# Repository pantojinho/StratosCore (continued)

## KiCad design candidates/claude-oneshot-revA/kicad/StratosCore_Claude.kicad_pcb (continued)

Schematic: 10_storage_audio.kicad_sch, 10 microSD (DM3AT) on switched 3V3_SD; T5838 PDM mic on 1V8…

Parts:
C120, C123: 100pF; C_0402_1005Metric
C121: 10uF; C_0603_1608Metric
C122, C125, C126: 100nF; C_0402_1005Metric
C124: 1uF; C_0402_1005Metric
C127: 100nF X7R; C_0402_1005Metric
J8: DM3AT-SF-PEJM5; Hirose_DM3AT-SF-PEJM5_microSD_HC; MPN DM3AT-SF-PEJM5
MK1: MMICT5838-00-012; TDK_T5838_LGA-7_3.5x2.65mm_BottomPort; MPN MMICT5838-00-012
R100, R104, R105, R106: 100k; R_0402_1005Metric
R101, R102, R103: 10k; R_0402_1005Metric
R107, R108: 47k; R_0402_1005Metric
TP27, TP28: TP; TestPoint_Pad_D1.0mm
U10, U12: TPS22918DBVR; TI_DBV0006A_SOT-23-6_TPS22918; MPN TPS22918DBVR
U23: TPD4E05U06DQAR; USON-10_2.5x1.0mm_P0.5mm; MPN TPD4E05U06DQARG4
U24: TXU0202DCUR; TI_DCU0008A_VSSOP-8_2.3x2mm_P0.5mm_TXU0202; MPN TXU0202DCUR

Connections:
1V8_AUDIO_SW: C124.1, C126.1, C127.1, MK1.7 (VDD), R106.2, U12.5 (QOD), U12.6 (VOUT), U24.7 (VCCB)
1V8_LOGIC: U12.1 (VIN); also elsewhere on the board
3V3_MAIN: C125.1, R104.2, U10.1 (VIN), U24.3 (VCCA); also elsewhere on the board
3V3_SD: C121.1, C122.1, J8.4 (VDD), R101.2, R102.2, R103.2, R107.2, R108.2, TP27.1, U10.5 (QOD), U10.6 (VOUT)
AUD_CT: C123.1, U12.4 (CT)
AUD_SW_EN: R105.1, U12.3 (ON); also elsewhere on the board
GND: C120.2, C121.2, C122.2, C123.2, C124.2, C125.2, C126.2, C127.2, J8.6 (VSS), J8.10 (DET_A), J8.SH (SHIELD), MK1.2 (SELECT), MK1.3 (GND), MK1.5 (THSEL), R100.2, R105.2, U10.2 (GND), U12.2 (GND), U23.3 (GND), U23.8 (GND), U24.2 (GND); also elsewhere on the board
PDM_CLK: U24.5 (A1); also elsewhere on the board
PDM_CLK_1V8: MK1.6 (CLK), U24.8 (B1Y)
PDM_DATA: U24.4 (A2Y); also elsewhere on the board
PDM_DATA_1V8: MK1.1 (DATA), U24.1 (B2)
PDM_OE: R106.1, U24.6 (OE)
SD_CD: J8.9 (DET_B), R104.1, TP28.1; also elsewhere on the board
SD_CS: J8.2 (DAT3/CD), R101.1, U23.1 (D1+), U23.10 (NC); also elsewhere on the board
SD_CT: C120.1, U10.4 (CT)
SD_DAT1: J8.8 (DAT1), R107.1
SD_DAT2: J8.1 (DAT2), R108.1
SD_SW_EN: R100.1, U10.3 (ON); also elsewhere on the board
SPI_MISO: J8.7 (DAT0), R103.1, U23.5 (D2-), U23.6 (NC); also elsewhere on the board
SPI_MOSI: J8.3 (CMD), R102.1, U23.2 (D1-), U23.9 (NC); also elsewhere on the board
SPI_SCLK: J8.5 (CLK), U23.4 (D2+), U23.7 (NC); also elsewhere on the board

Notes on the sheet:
10 microSD (DM3AT) on switched 3V3_SD; T5838 PDM mic on 1V8_AUDIO_SW
DIG-02: SPI mode (DAT3 = SD_CS), 10k pull-ups on CMD/DAT0/DAT3 to 3V3_SD (never 3V3_MAIN), no CLK pull-up, card detect 100k to 3V3_MAIN on TCA P00, TPD4E05U06 at the socket.
AUD-01/AUD-02: 1V8_AUDIO_SW = TPS22918 branch from 1V8_LOGIC (AUD_SW_EN, pull-down). TXU0202 A1->B1Y clock, B2->A2Y data, OE 100k to 1V8_AUDIO_SW.
T5838 SELECT=GND (DATA1/right), THSEL=GND and WAKE open (no AAD). 0.8 mm sound hole in the footprint, no paste on the port.

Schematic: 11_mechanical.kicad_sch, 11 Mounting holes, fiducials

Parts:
FID1, FID2, FID3: Fiducial; Fiducial_1mm_Mask2mm
H1, H2, H3: M2.5; MountingHole_2.7mm_M2.5

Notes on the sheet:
11 Mounting holes, fiducials
Three M2.5 mounting holes in the left strip (the 2S holder covers the back for x > 14.7 mm; holder is fixed to the rear shell); three fiducials.

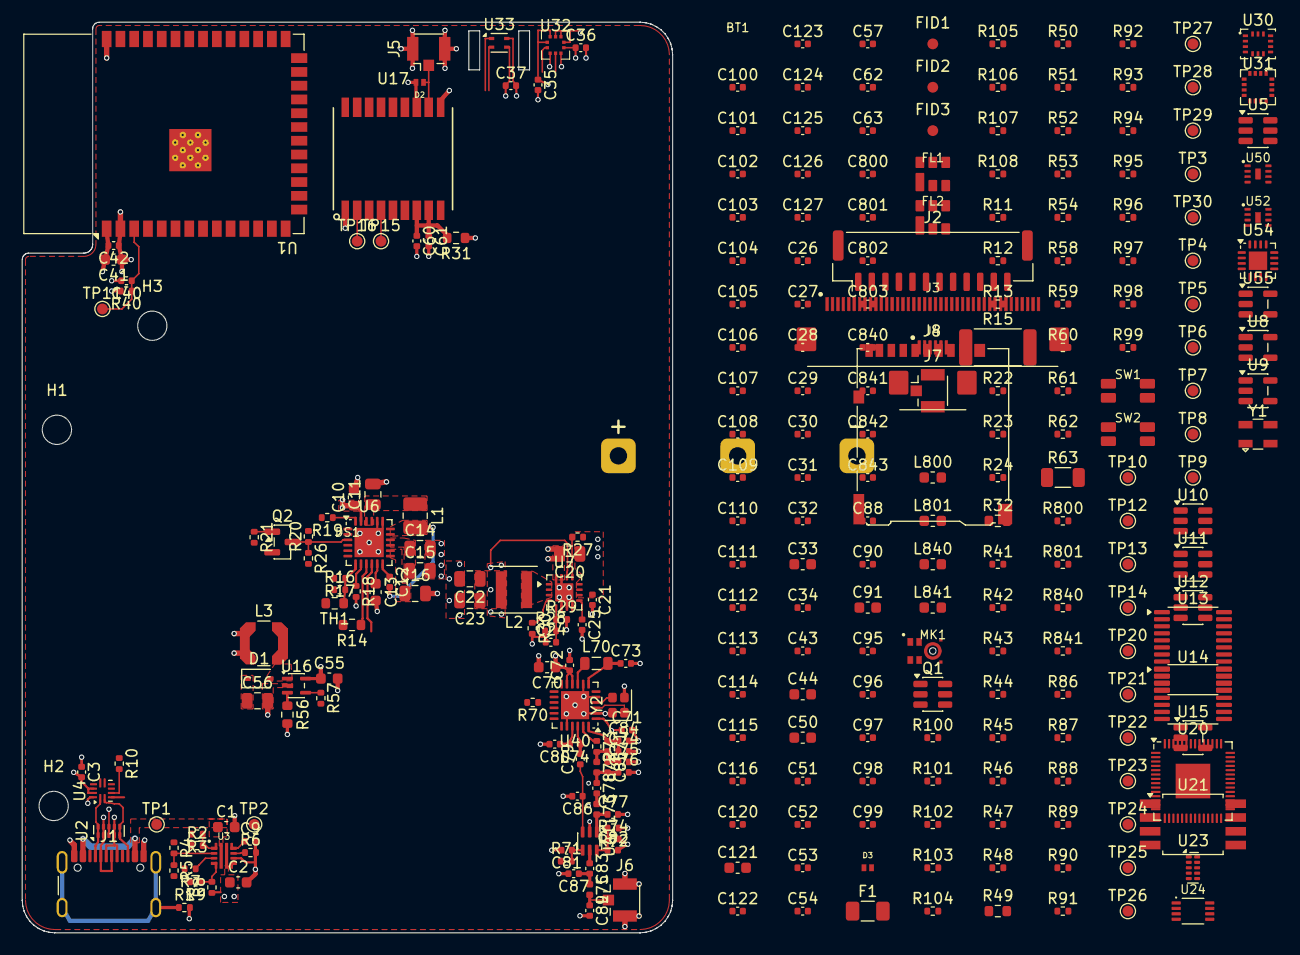
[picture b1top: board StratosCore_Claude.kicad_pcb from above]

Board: 4 copper layers, 60.0 x 84.0 mm, 293 parts (0 on the bottom side), 178 nets.

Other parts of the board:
DS1: display envelope; Display_Orient_AFY240320A1-2.8INTH-C1_Envelope

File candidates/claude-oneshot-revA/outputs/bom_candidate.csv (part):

"Refs","Value","Footprint","MPN","Status","Source","Qty","DNP"
"BT1","2S 21700 holder (MPN TBD)","SC:BatteryHolder_2S_21700_TBD","TBD","OWNER DIRECTION - MPN/REVIEW TBD","","1",""
"C1,C2","1uF 25V X7R","Capacitor_SMD:C_0603_1608Metric","","","","2",""
"C3,C30,C35-C37,C42,C43,C51-C54,C57,C61-C63,C72,C97,C100-C107,C110-C113,C116,C122,C125,C126","100nF","Capacitor_SMD:C_0402_1005Metric","","ADC_AVDD,USB_VDD","","33",""
"C9","TBD (O06)","Capacitor_SMD:C_0402_1005Metric","","ITIMER value TBD at O06","","1","DNP"
"C10","1uF 25V","Capacitor_SMD:C_0603_1608Metric","","","","1",""
"C11","10uF 25V","Capacitor_SMD:C_0805_2012Metric","","","","1",""
"C12,C95,C96","47nF","Capacitor_SMD:C_0402_1005Metric","","","","3",""
"C13,C55","4.7uF 10V","Capacitor_SMD:C_0603_1608Metric","","","","2",""
"C14,C15","22uF 16V","Capacitor_SMD:C_0805_2012Metric","","","","2",""
"C16","10uF 16V","Capacitor_SMD:C_0805_2012Metric","","","","1",""
"C20","10uF 25V X7R","Capacitor_SMD:C_0805_2012Metric","","","","1",""
"C21","100nF 25V","Capacitor_SMD:C_0402_1005Metric","","","","1",""
"C22,C23","22uF 6.3V X7R","Capacitor_SMD:C_0805_2012Metric","","second output cap; DC-bias review","","2",""
"C24,C25","3.3nF","Capacitor_SMD:C_0402_1005Metric","","feed-forward per repo text; review","","2",""
"C26-C29,C34,C40,C108,C109,C124","1uF","Capacitor_SMD:C_0402_1005Metric","","VREG_VIN,VREG_VOUT","","9",""
"C31","2.2uF","Capacitor_SMD:C_0402_1005Metric","","","","1",""
"C32","10nF","Capacitor_SMD:C_0402_1005Metric","","VDDIO decoupling (DS)","","1",""
"C33,C41,C44,C50,C70,C91,C121","10uF","Capacitor_SMD:C_0603_1608Metric","","SET/RESET capacitor per DS","","7",""
"C56","1uF 50V X7R","Capacitor_SMD:C_0805_2012Metric","","","","1",""
"C60","1uF X7R","Capacitor_SMD:C_0402_1005Metric","","","","1",""
"C71,C73","470nF","Capacitor_SMD:C_0402_1005Metric","","VREG decoupling; value per E449 BOM TBD","","2",""
"C74-C80,C83","TBD (E449)","Capacitor_SMD:C_0402_1005Metric","","DC block to PE4259 RF1; value TBD,RX balun series C; value TBD,RX balun shunt; value TBD,TX match shunt; value TBD,VR_PA decoupling; value TBD,antenna DC block; value TBD,pi-filter shunt; value TBD","","8",""
"C81,C82","1nF","Capacitor_SMD:C_0402_1005Metric","","AN1200.40 C14,AN1200.40 C15","","2",""
"C88","100nF","Capacitor_SMD:C_0402_1005Metric","","","","1","DNP"
"C90,C98,C120,C123,C800,C802,C840,C842","100pF","Capacitor_SMD:C_0402_1005Metric","","BLB01 EVB C1,BLB01 EVB C4","","8",""
"C99","1nF","Capacitor_SMD:C_0402_1005Metric","","basic value 1nF slows pulses; DNP pending bench","","1","DNP"
"C114,C115","15pF C0G","Capacitor_SMD:C_0402_1005Metric","","","","2",""
"C127","100nF X7R","Capacitor_SMD:C_0402_1005Metric","","DS: 0.1uF at pin 7","","1",""
"C801,C803,C841,C843","12pF","Capacitor_SMD:C_0402_1005Metric","","BLB01 EVB C2 (RF out),BLB01 EVB C3","","4",""
"D1","60V Schottky TBD","Diode_SMD:D_SOD-123F","","exact 60 V-class part TBD (open)","","1",""
"D2","TPD1E0B04DPYR","SC:TI_TPD1E0B04DPYR_X1SON-2_DPY0002A","TPD1E0B04DPYR","","","1",""
"D3","TPD1E0B04DPYR (option)","SC:TI_TPD1E0B04DPYR_X1SON-2_DPY0002A","","ESD option at ADS-B input - DNP until RF review","","1","DNP"
"F1","TBD (O05)","Fuse:Fuse_1206_3216Metric","","Rating/type TBD by qualified review (O05)","","1",""
"FL1,FL2","TA2003A 1090MHz SAW","SC:TAI-SAW_TA2003A_SMD-6_3.0x3.0mm","TA2003A","","","2",""
"J1","USB4105-GF-A","Connector_USB:USB_C_Receptacle_GCT_USB4105-xx-A_16P_TopMnt_Horizontal","USB4105-GF-A","PREFERRED CANDIDATE - drawing B4 second pass open","https://gct.co/files/drawings/usb4105.pdf","1",""
"J2","BM12B-GHS-TBT (expansion)","Connector_JST:JST_GH_BM12B-GHS-TBT_1x12-1MP_P1.25mm_Vertical","BM12B-GHS-TBT","pinout = CONNECTOR_ARCHITECTURE.md; ESD/hot-plug TBD","","1",""
"J3","XF3M-4015-1B (TFT 40p FPC)","SC:Omron_XF3M-4015-1B_1x40-1MP_P0.5mm_Horizontal","XF3M-4015-1B","SAMPLE/CONTROLLED-DRAWING HOLD (O01); footprint from Omron G146-E1 lands","","1",""
"J4","XF3M-0615-1B (CTP 6p FPC)","SC:Omron_XF3M-0615-1B_1x06-1MP_P0.5mm_Horizontal","XF3M-0615-1B","SAMPLE HOLD; ST1633I address 0x70 convention open","","1",""
"J5","U.FL-R-SMT-1(60) GNSS","SC:Hirose_U.FL-R-SMT-1_60_Vertical","U.FL-R-SMT-1(60)","","","1",""
"J6","U.FL-R-SMT-1(60) LoRa","SC:Hirose_U.FL-R-SMT-1_60_Vertical","U.FL-R-SMT-1(60)","","","1",""
"J7","U.FL-R-SMT-1(60) ADS-B","SC:Hirose_U.FL-R-SMT-1_60_Vertical","U.FL-R-SMT-1(60)","","","1",""
"J8","DM3AT-SF-PEJM5","SC:Hirose_DM3AT-SF-PEJM5_microSD_HC","DM3AT-SF-PEJM5","","Hirose drawing 0000947170 Rev 4","1",""
"L1","1uH (DFE252012F-1R0 class)","Inductor_SMD:L_1008_2520Metric","","TI Fig.69 value; saturation/DCR review","","1",""
"L2","2.2uH XFL4020-222MEB","SC:L_Coilcraft_XxL4020","XFL4020-222MEB","","","1",""
"L3","10uH LPS4018-103MRC","SC:L_Coilcraft_LPS4018","LPS4018-103MRC","","","1",""
"L70","15uH (DC-DC)","Inductor_SMD:L_0805_2012Metric","","AN1200.40 L7 15uH; exact part/ISAT TBD","","1",""
"L71-L74","TBD (E449)","Inductor_SMD:L_0402_1005Metric","","PA supply choke VR_PA->RFO; value TBD,RX balun series L; value TBD,TX match/notch series; value TBD,pi-filter series; value TBD","","4",""
"L800,L840","27nH","Inductor_SMD:L_0603_1608Metric","","BLB01 EVB L1","","2",""
"L801,L841","82nH","Inductor_SMD:L_0603_1608Metric","","BLB01 EVB L2","","2",""
"MK1","MMICT5838-00-012","SC:TDK_T5838_LGA-7_3.5x2.65mm_BottomPort","MMICT5838-00-012","PREFERRED CANDIDATE - acoustic/footprint review","","1",""
"Q1","Dual N-MOSFET TBD (O05)","Package_TO_SOT_SMD:SOT-23-6","","PLACEHOLDER - FET selection/SOA/package TBD (O05)","","1",""
"Q2","2N7002","Package_TO_SOT_SMD:SOT-23","","","","1",""
"R1,R53-R55,R96,R801,R841","0R","Resistor_SMD:R_0402_1005Metric","","BLB01 EVB R2,GPIO8 host control of translator OE (optional),Shield/chassis treatment TBD,unused RD tie TBD,unused WR(D/CX) tie TBD","","7",""
"R2,R8","232k 1%","Resistor_SMD:R_0402_1005Metric","","one-shot candidate","","2",""
"R3,R5,R9,R29","100k 1%","Resistor_SMD:R_0402_1005Metric","","one-shot candidate","","4",""
"R4","442k 1%","Resistor_SMD:R_0402_1005Metric","","","","1",""
"R6","1.69k 1%","Resistor_SMD:R_0402_1005Metric","","","","1",""
"R7,R11-R13,R20,R21,R27,R30,R46-R48,R51,R57,R70,R90,R100,R104-R106","100k","Resistor_SMD:R_0402_1005Metric","","P10 default released,default OFF,default OFF (DIG-03),fail-safe: charge disabled","","19",""
"R10","900k 1%","Resistor_SMD:R_0402_1005Metric","","data-sheet 900k","","1",""
"R14","300R","Resistor_SMD:R_0603_1608Metric","","TI reverse-bottom-cell limiter","","1",""
"R15","TBD (RCBSET)","Resistor_SMD:R_2512_6332Metric","","balance current TBD; 40.8R/0.41W at 100 mA planning point","","1",""
"R16","5.23k 1%","Resistor_SMD:R_0402_1005Metric","","","","1",""
"R17","30.1k 1%","Resistor_SMD:R_0402_1005Metric","","","","1",""
"R18","2.21k 1%","Resistor_SMD:R_0402_1005Metric","","IINMAX = 1110/2210 = 502 mA (default-current floor)","","1",""
"R19,R22-R24,R40-R42,R45,R50,R52,R58,R91,R101-R103","10k","Resistor_SMD:R_0402_1005Metric","","PSEL high = low input-current class","","15",""
"R26","0R","Resistor_SMD:R_0402_1005Metric","","SERVICE OVERRIDE ONLY - DNP","","1","DNP"
"R28","312k 1%","Resistor_SMD:R_0402_1005Metric","","","","1",""
"R31,R32,R49","0R","Resistor_SMD:R_0603_1608Metric","","GNSS branch; bead DCR<=0.15R fallback (GNSS-01),TFT VCC link (O01 power clarification),expansion current limit TBD","","3",""
"R43,R44,R98","2.2k 1%","Resistor_SMD:R_0402_1005Metric","","ADSB-01","","3",""
"R56","2.21R 1% 0.1W","Resistor_SMD:R_0603_1608Metric","","","","1",""
"R60,R61","470R","Resistor_SMD:R_0402_1005Metric","","ABLIC Table 11 typ,ABLIC Table 11 typ; R1*C1 = R2*C2","","2",""
"R62","2k","Resistor_SMD:R_0402_1005Metric","","ABLIC Table 11 typ","","1",""
"R71,R72","100R","Resistor_SMD:R_0402_1005Metric","","AN1200.40 R3,AN1200.40 R4","","2",""
"R86,R87","TBD (OWN-09)","Resistor_SMD:R_0402_1005Metric","","threshold divider BLOCKED by OWN-09","","2",""
"R88","10k","Resistor_SMD:R_0402_1005Metric","","optional RP2040 PWM threshold","","1","DNP"
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
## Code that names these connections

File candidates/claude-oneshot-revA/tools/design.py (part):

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    # ======================================================================= 04 compute + control
    d.sheet("04 Compute and control", "04_compute.kicad_sch",
            "04 ESP32-S3-WROOM-1-N16R8, buttons, TCA9535 slow control, I2C pull-ups, expansion", [
        "GPIO allocation = docs/INTERFACE_GPIO_MAP.md. GPIO3/45/46 straps and GPIO35-37 (octal PSRAM) are no-connect.",
        "TCA9535 map = docs/CONTROL_IO_REVIEW.md DIG-03 plus candidate decisions of 2026-09-24: A5 GPIO8 = EXP_CS_N (hardware SPI CS), A8 P07 = TOUCH_RST_N (10k pull-down),",
        "P10 SX_NRESET (was reserved SX aux), P14 RP_RUN (DIG-01 host reset), P15 BUCK_PG (input), P17 CHG_EN (charger enable, hardware default = disabled).",
        "I2C 100 kHz, 2.2k pull-ups on 3V3_MAIN (D22). JST GH BM12B-GHS-TBT is a VERTICAL (top-entry) header in JST/KiCad naming, not right-angle as the BOM text says.",
    ])
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          "Connector_JST:JST_GH_BM12B-GHS-TBT_1x12-1MP_P1.25mm_Vertical",
          {"1": "GND", "2": "3V3_EXP", "3": "I2C_SDA", "4": "I2C_SCL", "5": "SPI_SCLK", "6": "GND",
           "7": "SPI_MOSI", "8": "SPI_MISO", "9": "EXP_CS_N", "10": "EXP_UART_TX", "11": "EXP_UART_RX",
           "12": "EXP_IRQ", "MP": "GND"}, mpn="BM12B-GHS-TBT", status="pinout = CONNECTOR_ARCHITECTURE.md; ESD/hot-plug TBD")
    d.C("C44", "10uF", "3V3_EXP", fp="C0603")
    d.flag("3V3_EXP")

    # ======================================================================= 05 display
    d.sheet("05 Display and touch", "05_display.kicad_sch",
            "05 Orient AFY240320A1-2.8INTH-C1: XF3M FPC connectors, 3.3->1.8 V SPI branch, reset, backlight", [
        "Write-only three-line 9-bit SPI, IM2/IM1/IM0 = 1/0/1 (rev J). SN74AXC4T245: DIR high (A->B), OE pulled low (always enabled; GPIO8 is now EXP_CS_N, A5-2).",
        "TFT reset: TCA9535 P06 LCD_RST_CTRL (100k pull-down) -> SN74LVC1G07 open drain -> 10k to 1V8_LOGIC (DSP-02). Touch RESET = TCA9535 P07 TOUCH_RST_N, 10k pull-down (A8-2).",
        "UNUSED-PIN TIES ARE TBD (gate 3): DB17..DB0, DOTCLK/DE/VSYNC/HSYNC tied to GND; RD/WR tied high through R53/R54 0R (swap to GND if the controller spec requires).",
        "TFT VCC fed from 3V3_MAIN (2.4-3.6 V range) - the VDD/VDDI contradiction in the Orient drawing is still open (O01). Backlight TPS61169: RSET 2.21R -> ~92 mA.",
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        "A2: RF network redrawn to the Semtech E449V01A / E428V03A reference topology (same RF values in both 902-928 MHz boards) with the reference BOM values as STARTING values.",
        "*** The values were tuned by Semtech on a 1.0 mm stack (0.15 mm L1-L2). On JLC04161H-3313 they must be re-tuned on a VNA and pass conducted TX power/harmonic/RX tests (AGENTS rule 5). Not validated. ***",
        "Crystal (E428-type) kept by the lowest-cost criterion: NDK NX2016SA 32 MHz EXS00A-CS06465 (CL 10 pF, +/-10 ppm). TCXO (E449) is the owner option if long-airtime plans are used; DIO3 left open.",
        "PE4259 single-pin mode: pin 6 = VDD through R72/R74 divider (about 3.09 V; pSemi operating range is 1.8-3.3 V and 3V3_MAIN can exceed 3.3 V with tolerance). DIO2 = 1 in TX selects RF1. No TX before a regional configuration (AGENTS rule 14).",
    ])
    E449 = "Semtech E449V01A BOM V1a (SX1262MB1PAS); see docs/review_notes/SX1262_E449_REFERENCE_VALUES.md"
    d.g("sx")
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          source="pSemi DOC-03694-5.01 Table 5")
    d.R("R71", "100R", "SX_DIO2", "LORA_SW_CTRL", status="E449 R3")
    d.C("C81", "1nF", "LORA_SW_CTRL", status="E449 C15")
    d.R("R72", "1k", "3V3_MAIN", "LORA_SW_VDD", status="A2: with R74 sets pin 6 to ~0.94 x 3V3_MAIN (<= 3.3 V operating max)")
    d.R("R74", "15k", "LORA_SW_VDD", "GND", status="A2: PE4259 VDD divider (IDD 9 uA typ)")
    d.C("C82", "1nF", "LORA_SW_VDD", status="E449 C14")
    d.C("C83", "39pF C0G", "LORA_RFC", "LORA_ANTF", status="E449 C8", source=E449)
    d.C("C87", "3.3pF C0G", "LORA_ANTF", status="E449 C9 - start value, tune", source=E449)
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    d.sheet("09 ADS-B receiver", "09_adsb.kicad_sch", "09 1090 MHz chain (BLB01 x2, TA2003A x2, ADL5513, MCP6566) and RP2040 capture", [
        "Chain per docs/ADSB_VALIDATION.md. BLB01 bias per BeRex rev 6.6 evaluation BOM (C1 100pF in, C2 12pF out, R1 6.8k/C3 12pF/L1 27nH Ven, R2 0R/C4 100pF/L2 82nH Vd).",
        "ADL5513 measurement mode (VSET=VOUT), 52.3R input termination, 47nF coupling. TADJ resistor and CLPF (1 nF basic value is too slow for 0.5 us pulses) are TBD/bench items.",
        "MCP6566T-E/OT base pin map, 2.2k pull-up to the RP2040 bank. A2: threshold = filtered RP2040 PWM (R88/C88/R87) with ADSB_VIDEO also sampled on ADC0 (R89); fixed-divider top R86 stays DNP (OWN-09 target still open).",
        "RP2040 per DIG-01 (Raspberry Pi minimal design): 12 MHz ABM8-272-T3 + 1k XOUT, 15pF loads; QSPI_SS 1k to USB_BOOT pad; RUN 10k/100nF + TCA9535 P14. Domain 3V3_ADSB switched (P13). A2: USB D+/D- on test pads through 27R so BOOTSEL (TP21) is usable.",
        "UART0: GPIO0 TX -> RP_UART_RX, GPIO1 RX <- RP_UART_TX, GPIO2 CTS <- RP_UART_RTS, GPIO3 RTS -> RP_UART_CTS (one-shot pin choice). Back-power of ESP32-driven lines into an OFF RP2040 is an open SYS-02 item.",
    ])
    d.g("adsbsw")
    d.add("U11", f"{PLIB}:TPS22918", "TPS22918DBVR", CUSTOM["TPS22918"]["fp"],
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    d.C("C116", "100nF", "3V0_RF_QUIET")
    d.R("R98", "2.2k 1%", "ADSB_PULSE", "3V3_ADSB", status="ADSB-01")
    d.R("R86", "TBD (OWN-09)", "3V0_RF_QUIET", "ADSB_THR", dnp=True, status="optional fixed-bias top resistor - DNP; value blocked by OWN-09")
    d.R("R87", "100k", "ADSB_THR", "GND", status="A2: defines 0 V threshold (comparator idle) while the RP2040 pin is high-Z; scales PWM full scale to ~3.0 V")
    d.R("R88", "10k", "ADSB_THR_PWM", "ADSB_THR", status="A2: fitted - firmware-adjustable threshold from RP2040 GPIO9 PWM (replaces the blocked fixed divider)")
    d.C("C88", "1uF", "ADSB_THR", status="A2: PWM filter, about 17 Hz corner with R88||R87")
    d.R("R89", "1k", "ADSB_VIDEO", "ADSB_VIDEO_ADC", status="A2: log-video level to RP2040 ADC0 (GPIO26) for noise-floor/threshold tracking; isolates the ADC sample cap from the fast video node")
    d.TP("TP25", "ADSB_VIDEO")
    d.TP("TP26", "ADSB_PULSE")

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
